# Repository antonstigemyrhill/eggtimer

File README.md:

# eggtimer
eggtimer for pcb design

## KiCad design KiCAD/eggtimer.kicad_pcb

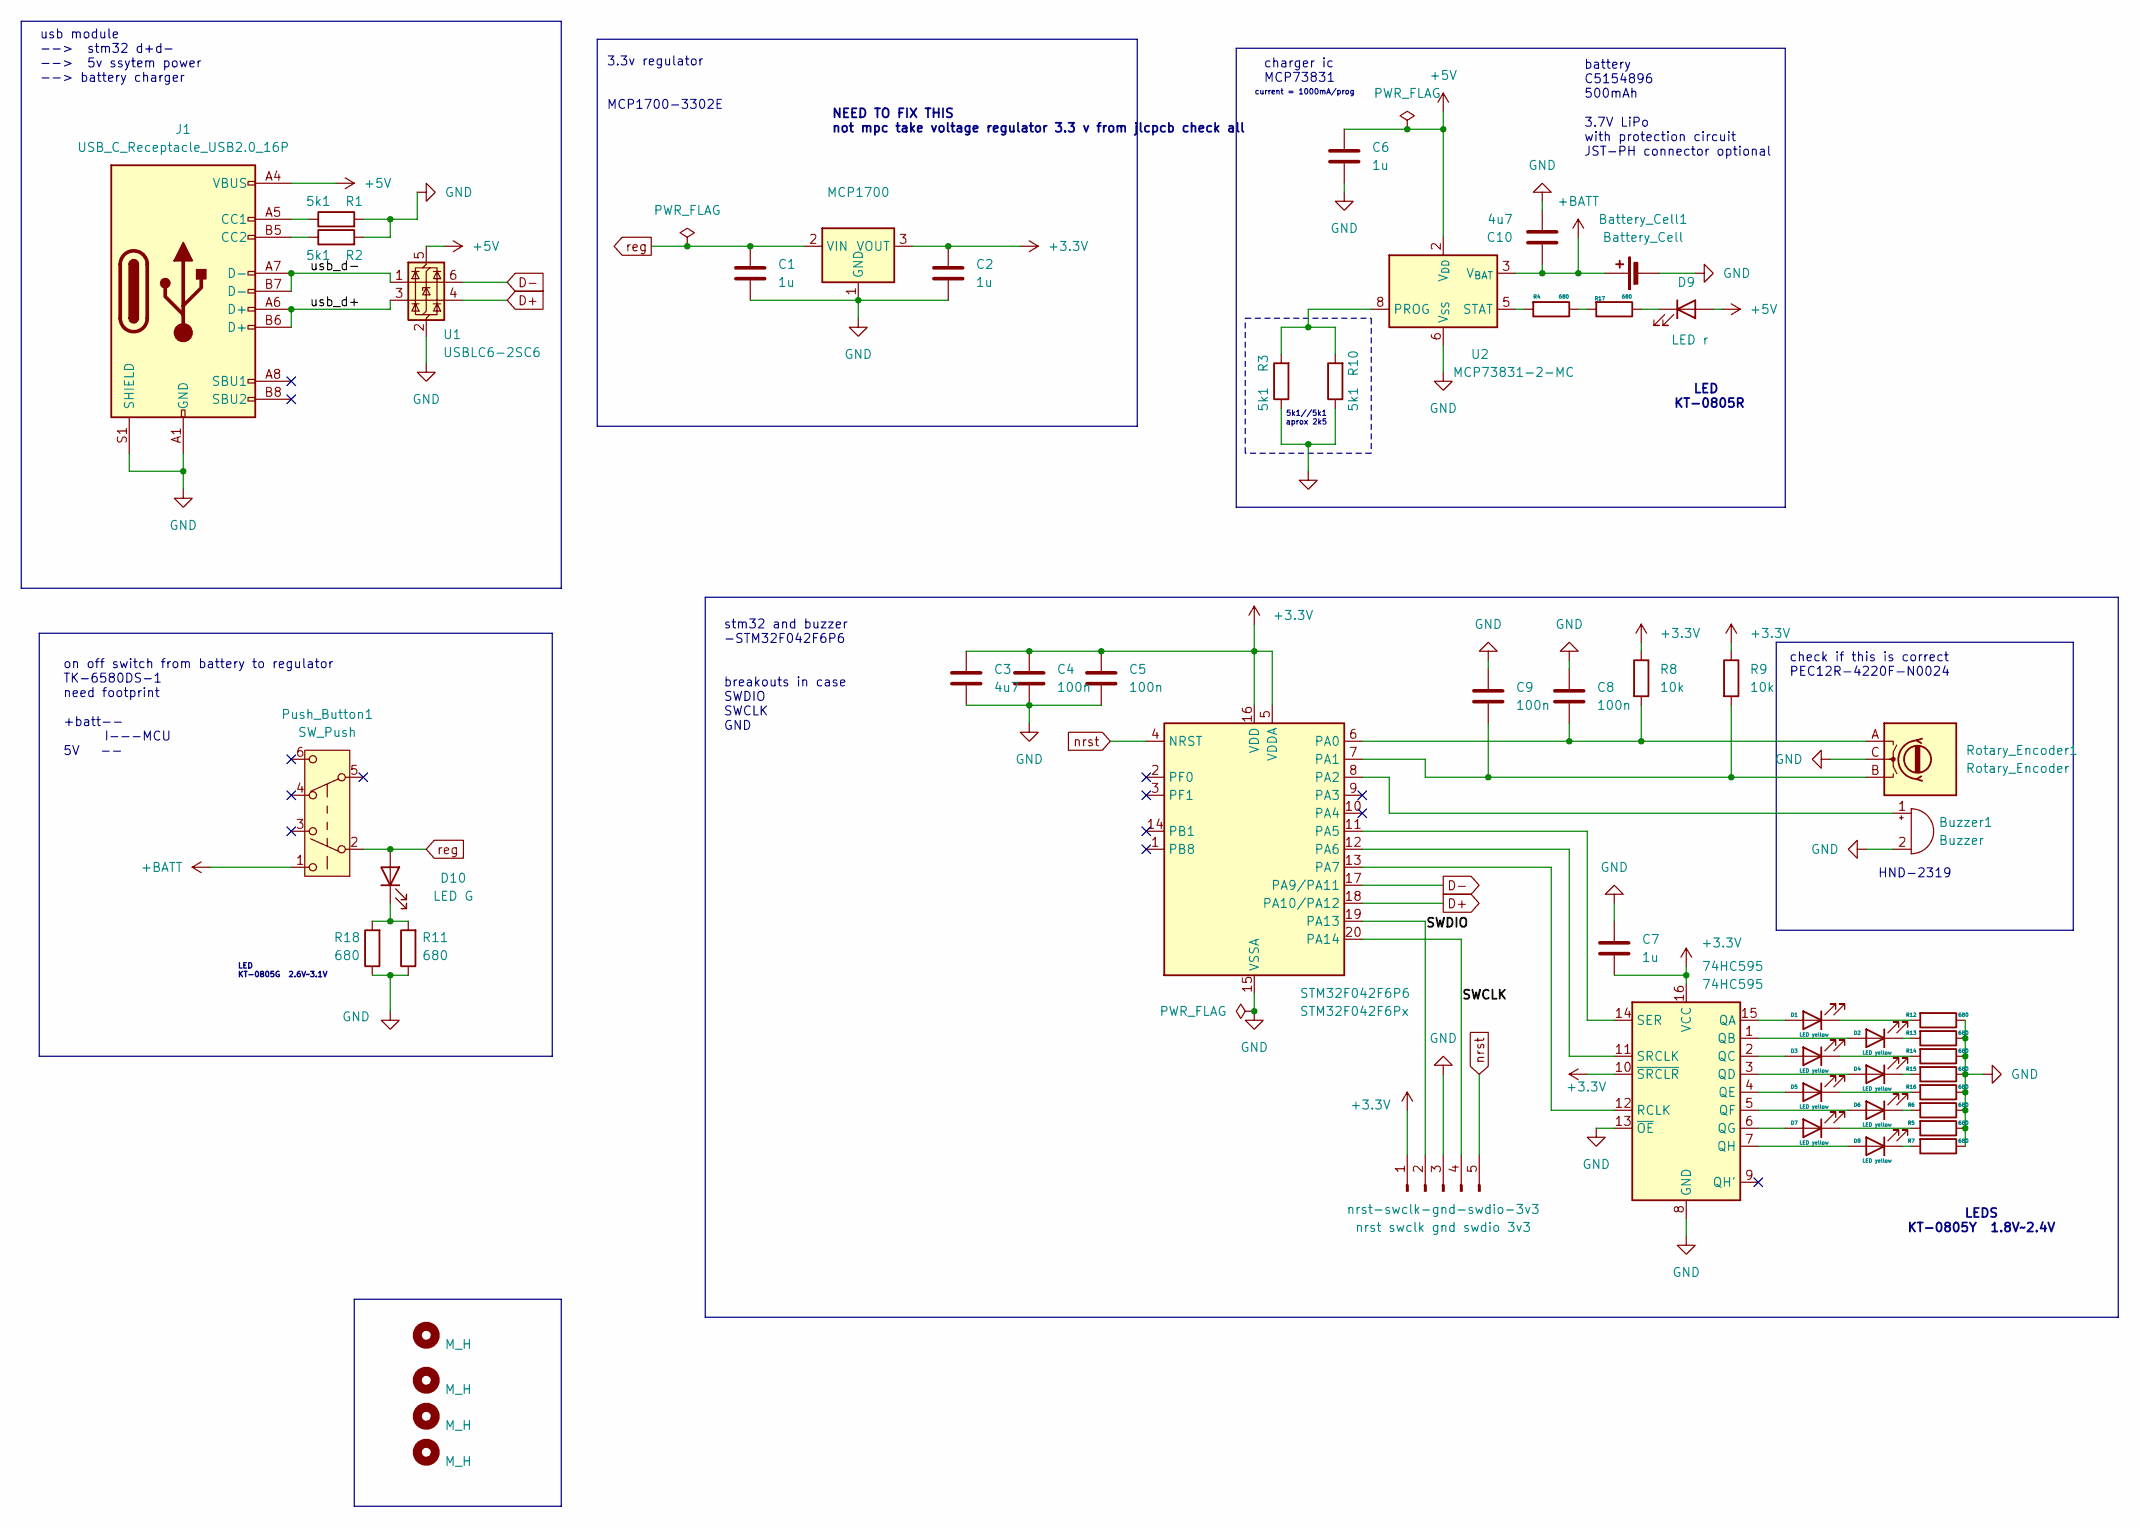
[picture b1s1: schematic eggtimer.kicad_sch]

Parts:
74HC595: 74HC595; 74HC595D,118 SOIC-16 Shift Registers
Battery_Cell1: Battery_Cell; screw_terminal_2
Buzzer1: Buzzer; HND-2319 Buzzer
C1, C2, C6, C7: 1u; C_0603_1608Metric
C3, C10: 4u7; C_0805_2012Metric
C4, C5, C8, C9: 100n; C_0402_1005Metric
D1, D2, D3, D4, D5, D6, D7, D8: LED yellow; LED_0805_2012Metric
D9: LED r; LED_0805_2012Metric
D10: LED G; LED_0805_2012Metric
H1, H2, H3, H4: M_H; MountingHole_2.2mm_M2
J1: USB_C_Receptacle_USB2.0_16P; USB_C_Receptacle_GCT_USB4105-xx-A_16P_TopMnt_Horizontal
MCP1700: SOT-89-3
Push_Button1: SW_Push; TK-6580DS-1 push button
R1, R2, R3, R10: 5k1; R_0603_1608Metric
R4, R5, R6, R7, R11, R12, R13, R14, R15, R16, R17, R18: 680; R_0402_1005Metric
R8, R9: 10k; R_0805_2012Metric
Rotary_Encoder1: Rotary_Encoder; PEC12R-4220F-N0024 encoder
STM32F042F6P6: STM32F042F6Px; TSSOP-20_4.4x6.5mm_P0.65mm
U1: USBLC6-2SC6; SOT-23-6
U2: MCP73831-2-MC; DFN-8-1EP_3x2mm_P0.5mm_EP1.7x1.4mm
nrst-swclk-gnd-swdio-3v3: nrst swclk gnd swdio 3v3; Harwin_LTek-Male_05_P2.00mm_Vertical

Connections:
+3.3V: 74HC595.10 (~SRCLR), 74HC595.16 (VCC), C2.1, C3.1, C4.1, C5.1, C7.2, MCP1700.3 (VOUT), R8.1, R9.1, STM32F042F6P6.5 (VDDA), STM32F042F6P6.16 (VDD), nrst-swclk-gnd-swdio-3v3.1; also elsewhere on the board
+5V: C6.2, D9.2 (A), J1.A4 (VBUS), J1.A9 (VBUS), J1.B4 (VBUS), J1.B9 (VBUS), U1.5 (VBUS), U2.1 (V_{DD}), U2.2 (V_{DD})
+BATT: Battery_Cell1.1 (+), C10.2, Push_Button1.1 (A), U2.3 (V_{BAT}), U2.4 (V_{BAT}); also elsewhere on the board
/SWCLK: STM32F042F6P6.20 (PA14), nrst-swclk-gnd-swdio-3v3.4
/SWDIO: STM32F042F6P6.19 (PA13), nrst-swclk-gnd-swdio-3v3.2
/usb_d+: J1.A6 (D+), J1.B6 (D+), U1.3 (I/O2)
/usb_d-: J1.A7 (D-), J1.B7 (D-), U1.1 (I/O1)
D+: STM32F042F6P6.18 (PA10/PA12), U1.4 (I/O2)
D-: STM32F042F6P6.17 (PA9/PA11), U1.6 (I/O1)
GND: 74HC595.8 (GND), 74HC595.13 (~OE), Battery_Cell1.2 (-), Buzzer1.2 (-), C1.2, C2.2, C3.2, C4.2, C5.2, C6.1, C7.1, C8.1, C9.1, C10.1, J1.A1 (GND), J1.A12 (GND), J1.B1 (GND), J1.B12 (GND), J1.S1 (SHIELD), MCP1700.1 (GND), R1.2, R2.2, R3.1, R5.1, R6.1, R7.1, R10.1, R11.1, R12.1, R13.1, R14.1, R15.1, R16.1, R18.1, Rotary_Encoder1.C, STM32F042F6P6.15 (VSSA), U1.2 (GND), U2.6 (V_{SS}), nrst-swclk-gnd-swdio-3v3.3; also elsewhere on the board
unnamed: 74HC595.15 (QA), D1.2 (A)
unnamed: 74HC595.1 (QB), D2.2 (A)
unnamed: 74HC595.2 (QC), D3.2 (A)
unnamed: 74HC595.3 (QD), D4.2 (A)
unnamed: 74HC595.4 (QE), D5.2 (A)
unnamed: 74HC595.5 (QF), D6.2 (A)
unnamed: 74HC595.6 (QG), D7.2 (A)
unnamed: 74HC595.7 (QH), D8.2 (A)
unnamed: 74HC595.12 (RCLK), STM32F042F6P6.13 (PA7)
unnamed: 74HC595.14 (SER), STM32F042F6P6.11 (PA5)
unnamed: 74HC595.11 (SRCLK), STM32F042F6P6.12 (PA6)
unnamed: Buzzer1.1 (+), STM32F042F6P6.8 (PA2)
unnamed: D1.1 (K), R12.2
unnamed: D2.1 (K), R13.2
unnamed: D3.1 (K), R14.2
unnamed: D4.1 (K), R15.2
unnamed: D5.1 (K), R16.2
unnamed: D6.1 (K), R6.2
unnamed: D7.1 (K), R5.2
unnamed: D8.1 (K), R7.2
unnamed: D9.1 (K), R17.1
unnamed: D10.1 (K), R11.2, R18.2
unnamed: J1.A5 (CC1), R1.1
unnamed: J1.B5 (CC2), R2.1
unnamed: R4.1, R17.2
unnamed: C8.2, R8.2, Rotary_Encoder1.A, STM32F042F6P6.6 (PA0)
unnamed: C9.2, R9.2, Rotary_Encoder1.B, STM32F042F6P6.7 (PA1)
unnamed: R3.2, R10.2, U2.8 (PROG)
unnamed: R4.2, U2.5 (STAT)
nrst: STM32F042F6P6.4 (NRST), nrst-swclk-gnd-swdio-3v3.5
reg: C1.1, D10.2 (A), MCP1700.2 (VIN), Push_Button1.2 (B); also elsewhere on the board

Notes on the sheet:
on off switch from battery to regulator TK-6580DS-1 need footprint +batt-- I---MCU 5V --
LEDS KT-0805Y 1.8V~2.4V
current = 1000mA/prog
usb module --> stm32 d+d- --> 5v ssytem power --> battery charger
LED KT-0805G 2.6V~3.1V
NEED TO FIX THIS not mpc take voltage regulator 3.3 v from jlcpcb check all
3.3v regulator MCP1700-3302E
LED KT-0805R
5k1//5k1 aprox 2k5
charger ic MCP73831
HND-2319
stm32 and buzzer -STM32F042F6P6 breakouts in case SWDIO SWCLK GND
check if this is correct PEC12R-4220F-N0024
battery C5154896 500mAh 3.7V LiPo with protection circuit JST-PH connector optional

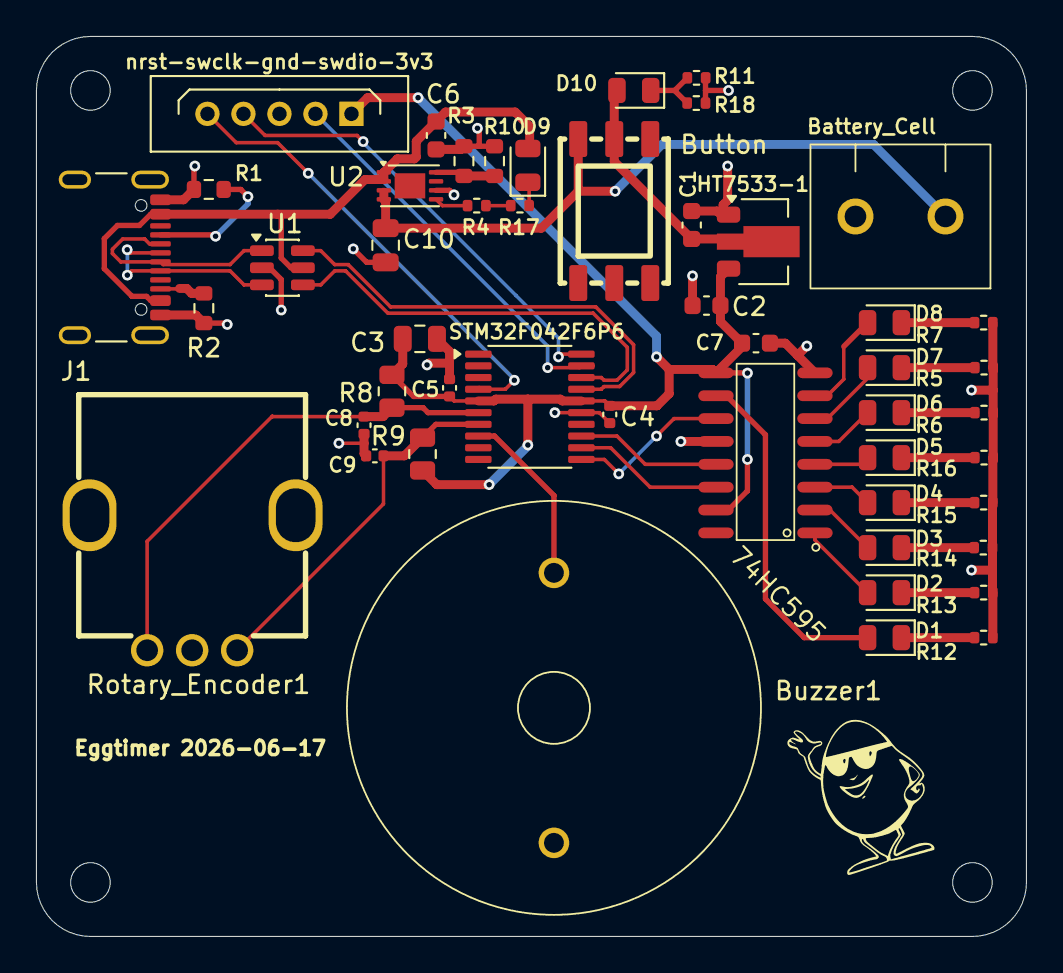
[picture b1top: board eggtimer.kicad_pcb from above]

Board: 2 copper layers, 55.0 x 50.0 mm, 54 parts (0 on the bottom side), 41 nets.

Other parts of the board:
Button: SW_Push; TK-6580DS-1 push button
HT7533-1: SOT-89-3
egg: LOGO

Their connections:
+3.3V: HT7533-1.3 (VOUT); also elsewhere on the board
+BATT: Button.1 (A); also elsewhere on the board
GND: HT7533-1.1 (GND); also elsewhere on the board
reg: Button.2 (B), HT7533-1.2 (VIN); also elsewhere on the board

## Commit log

2026-06-08 first KiCAD files
2026-06-08 fix: setup
2026-06-11 updated schematic
2026-06-11 custom footprints
2026-06-16 pcb: all done except battery, and debug pins
2026-06-17 Add files via upload
    KiCAD: need to fix BOM
2026-06-18 final
